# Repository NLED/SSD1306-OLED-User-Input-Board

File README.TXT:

THERE IS NO WARRANTY FOR THE PROGRAM, TO THE EXTENT PERMITTED BY APPLICABLE LAW. 
EXCEPT WHEN OTHERWISE STATED IN WRITING THE COPYRIGHT HOLDERS AND/OR OTHER PARTIES 
PROVIDE THE PROGRAM “AS IS” WITHOUT WARRANTY OF ANY KIND, EITHER EXPRESSED OR IMPLIED,
INCLUDING, BUT NOT LIMITED TO, THE IMPLIED WARRANTIES OF MERCHANTABILITY AND FITNESS 
FOR A PARTICULAR PURPOSE. THE ENTIRE RISK AS TO THE QUALITY AND PERFORMANCE OF THE 
PROGRAM IS WITH YOU. SHOULD THE PROGRAM PROVE DEFECTIVE, YOU ASSUME THE COST OF ALL 
NECESSARY SERVICING, REPAIR OR CORRECTION.

 Original Author: Jeffrey Nygaard
 Company: Northern Lights Electronic Design, LLC
 Date: July 26, 2018
 Contact: JNygaard@NLEDshop.com
 Copyright© 2018 by Northern Lights Electronic Design, LLC. All Rights Reserved
 
;=============          www.NLEDShop.com/oleddisplay          ============
;=============     www.NorthernLightsElectronicDesign.com       ============

This work is licensed under a Attribution-NonCommercial 4.0 International (CC BY-NC 4.0)
https://creativecommons.org/licenses/by-nc/4.0/legalcode

Free to use for personal use, but please attribute the original author.

Commercial licenses versions are available for a donation of any amount. Contact JNygaard@NLEDshop.com for details.

================================================================================================================

Ready-made devices are available for purchase, and large batch manufacturing of any device can be requested.
Please see the webpage www.NLEDShop.com/oleddisplay

NLED is available for custom design and manufacturing, please contact via phone or email to discuss your project.

================================================================================================================

Input Voltage: 3.3 volts

BOM:
3x FSM4JH momentary push button
1x SSD1306 128x32 OLED display with I2C carrier board - aliexpress/ebay
1x 3mm LED(optional) - requires external current resistor
1x compatible JST PH header, straight OR right angle, 2 positions to choose from
1x 8-pin JST PH 2.0mm wire harness

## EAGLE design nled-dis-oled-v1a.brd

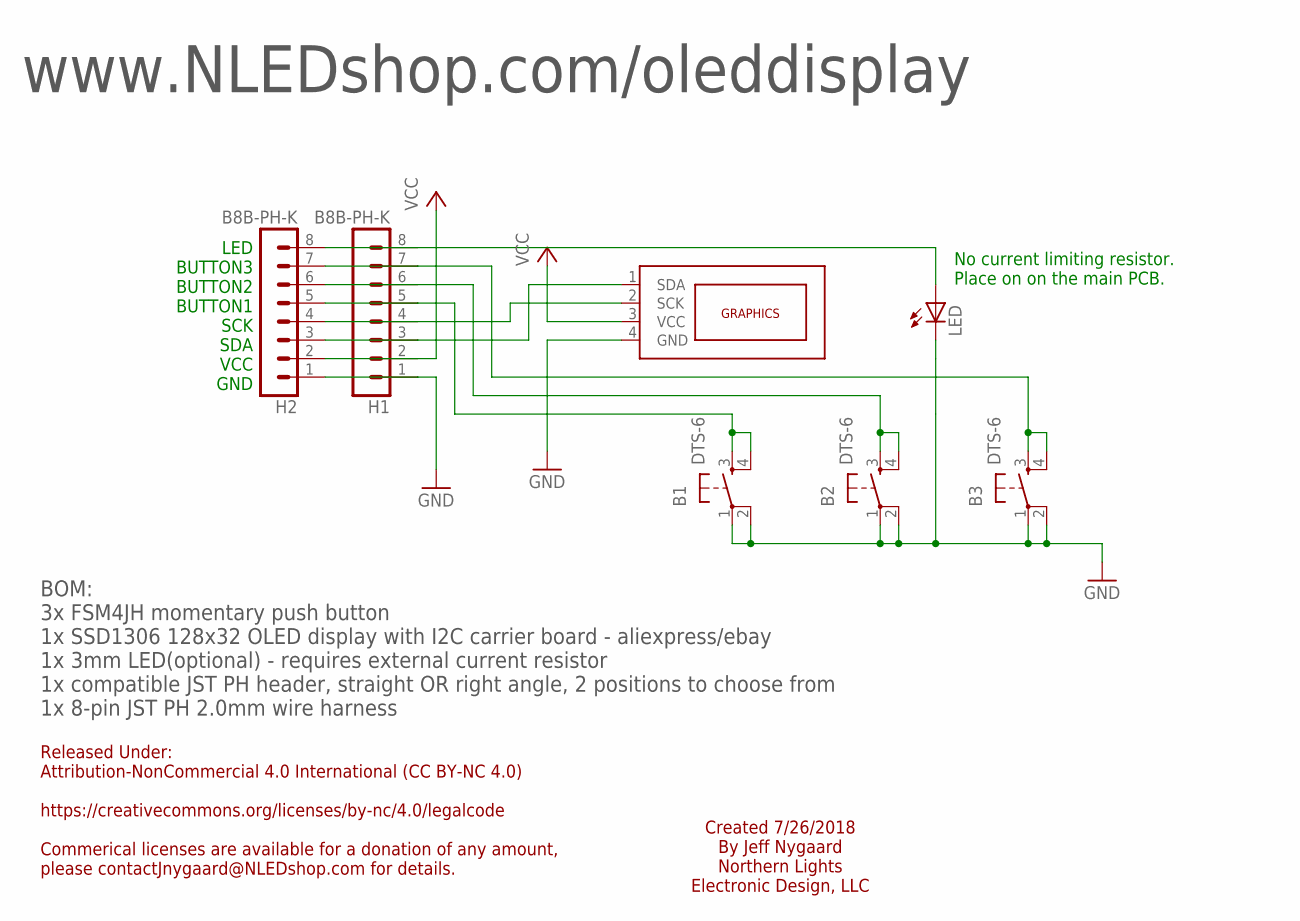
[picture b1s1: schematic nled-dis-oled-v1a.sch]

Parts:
B1, B2, B3: DTS-6
H1, H2: B8B-PH-K
LED: LED3MM
OLED: OLED-128X32

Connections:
GND: B1.1, B1.2, B2.1, B2.2, B3.1, B3.2, H1.1, H2.1, LED.K (C), OLED.4 (GND)
unnamed: H1.8, H2.8, LED.A
unnamed: B1.3, B1.4, H1.5, H2.5
unnamed: B2.3, B2.4, H1.6, H2.6
unnamed: B3.3, B3.4, H1.7, H2.7
unnamed: H1.3, H2.3, OLED.1 (SDA)
unnamed: H1.4, H2.4, OLED.2 (SCK)
VCC: H1.2, H2.2, OLED.3 (VCC)

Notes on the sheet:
No current limiting resistor. Place on on the main PCB.
LED BUTTON3 BUTTON2 BUTTON1 SCK SDA VCC GND
Released Under: Attribution-NonCommercial 4.0 International (CC BY-NC 4.0) https://creativecommons.org/licenses/by-nc/4.0/legalcode Commerical licenses are available for a donation of any amount, please contactJnygaard@NLEDshop.com for details.
Created 7/26/2018 By Jeff Nygaard Northern Lights Electronic Design, LLC
BOM: 3x FSM4JH momentary push button 1x SSD1306 128x32 OLED display with I2C carrier board - aliexpress/ebay 1x 3mm LED(optional) - requires external current resistor 1x compatible JST PH header, straight OR right angle, 2 positions to choose from 1x 8-pin JST PH 2.0mm wire harness
www.NLEDshop.com/oleddisplay

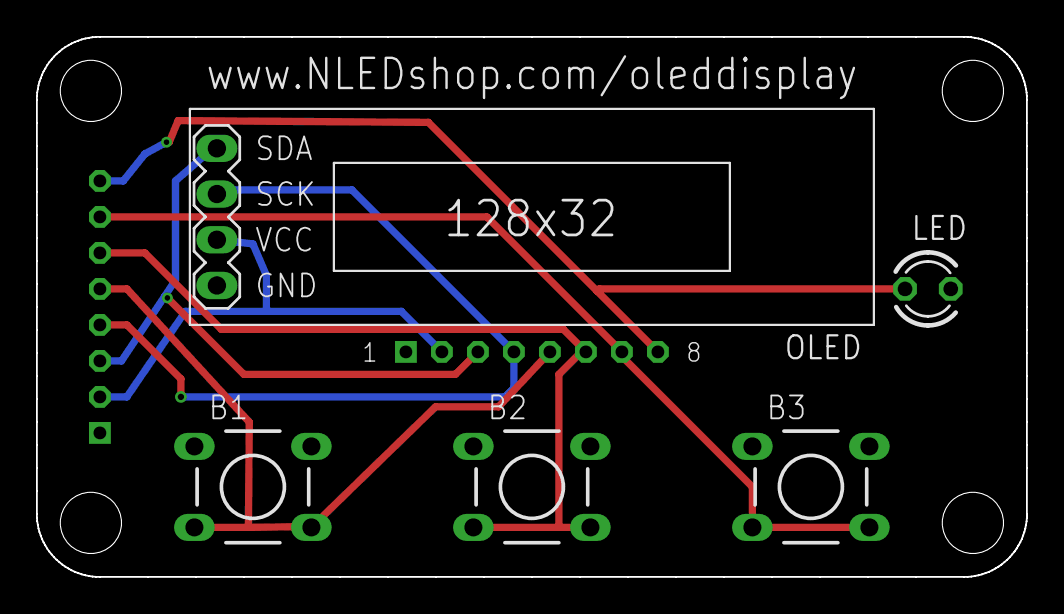
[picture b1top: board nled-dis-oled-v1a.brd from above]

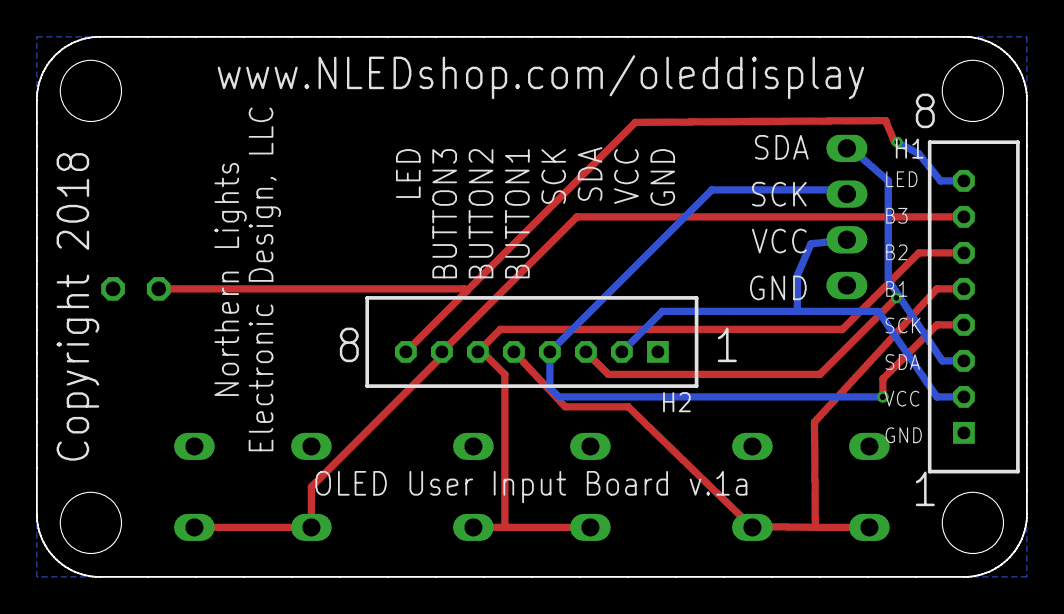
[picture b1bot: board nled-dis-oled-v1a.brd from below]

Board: 2 copper layers, 55.0 x 30.0 mm, 7 parts (2 on the bottom side), 8 nets.

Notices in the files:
nled-dis-oled-v1a.brd:
Copyright 2018
parts and their libraries:
con-jst-ph: Copyright (C) 2016, Bob Starr
